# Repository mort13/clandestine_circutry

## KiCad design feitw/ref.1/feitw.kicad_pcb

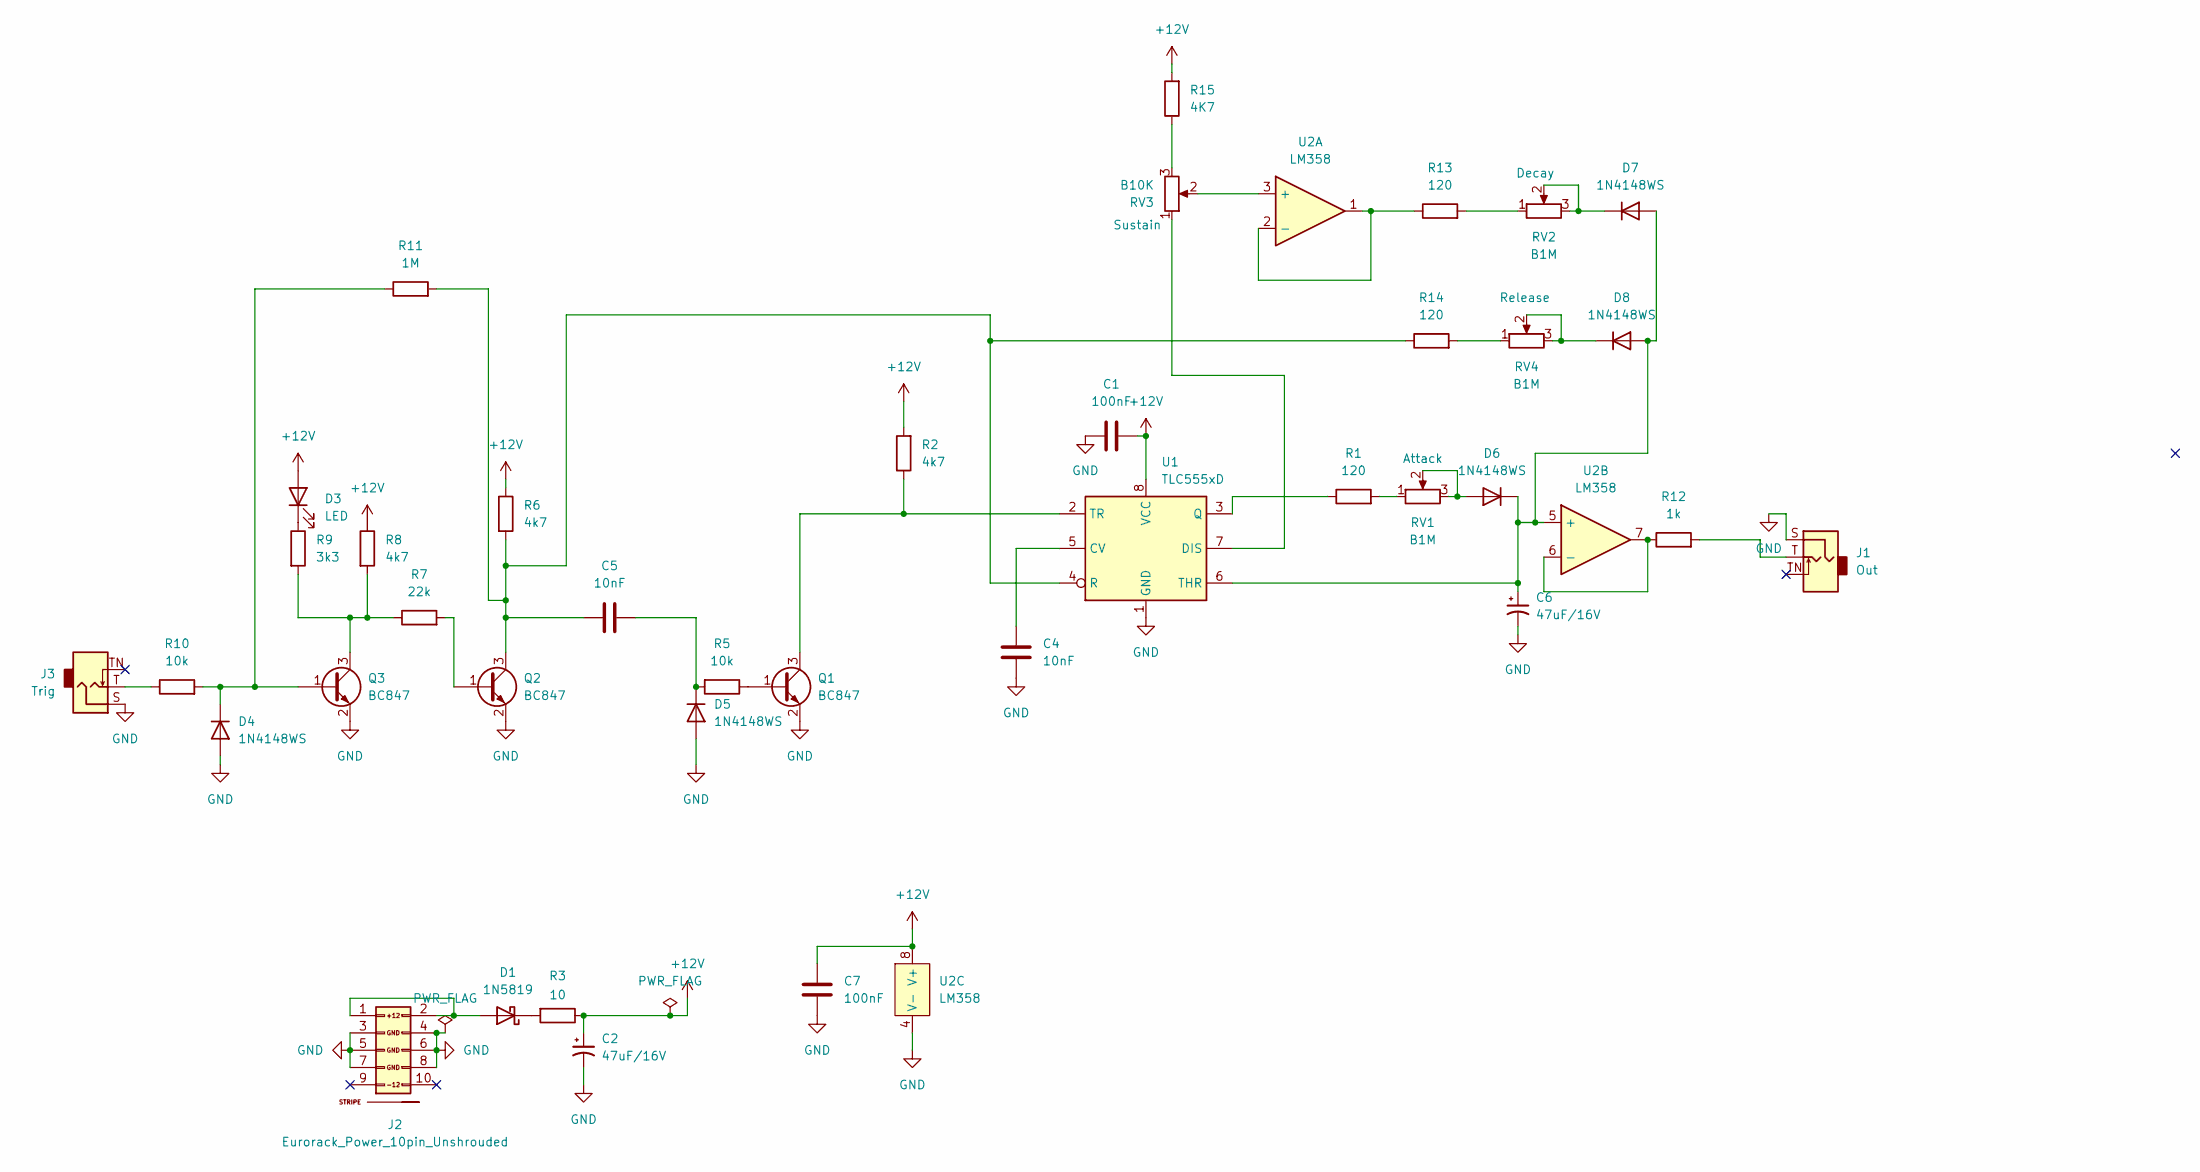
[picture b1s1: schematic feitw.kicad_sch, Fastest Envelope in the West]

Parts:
C1, C7: 100nF; C_Disc_D3.0mm_W1.6mm_P2.50mm
C2: 10uF_5x5.3_16V; CP_Radial_D4.0mm_P2.00mm; Part Number VE-470M1CTR-0505; JLCPCB ID C134798
C4, C5: 10nF; C_Disc_D3.0mm_W1.6mm_P2.50mm
C6: 47uF_5x5.3_16V; CP_Radial_D4.0mm_P2.00mm; Part Number VE-470M1CTR-0505; JLCPCB ID C134798
D1: 1N5819; D_DO-41_SOD81_P2.54mm_Vertical_AnodeUp
D3: LED; LED_D1.8mm_W3.3mm_H2.4mm
D4, D5, D6, D7, D8: 1N4148WS; D_SOD-323
J1: Out; PJ398SM
J2: Eurorack_Power_10pin_Unshrouded; PinSocket_2x05_P2.54mm_Vertical; Part Number 1-1002FBV0T
J3: Trig; PJ398SM
Q1, Q2, Q3: BC847; SOT-23
R1, R13, R14: 120; R_Axial_DIN0204_L3.6mm_D1.6mm_P1.90mm_Vertical
R2, R6, R8: 4k7; R_Axial_DIN0204_L3.6mm_D1.6mm_P1.90mm_Vertical
R3: 10; R_Axial_DIN0204_L3.6mm_D1.6mm_P1.90mm_Vertical
R5, R10: 10k; R_Axial_DIN0204_L3.6mm_D1.6mm_P1.90mm_Vertical
R7: 22k; R_Axial_DIN0204_L3.6mm_D1.6mm_P1.90mm_Vertical
R9: 3k3; R_Axial_DIN0204_L3.6mm_D1.6mm_P1.90mm_Vertical
R11: 1M; R_Axial_DIN0204_L3.6mm_D1.6mm_P1.90mm_Vertical
R12: 1k; R_Axial_DIN0204_L3.6mm_D1.6mm_P1.90mm_Vertical
R15: 4K7; R_Axial_DIN0204_L3.6mm_D1.6mm_P1.90mm_Vertical
RV1, RV2, RV4: B1M; Potentiometer_Alpha_RD901F-40-00D_Single_Vertical_withhole
RV3: B10K; Potentiometer_Alpha_RD901F-40-00D_Single_Vertical_withhole
U1: TLC555xD; SOIC-8_3.9x4.9mm_P1.27mm
U2: LM358; SOIC-8_3.9x4.9mm_Pitch1.27mm; JLCPCB ID C7951

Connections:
+12V: C1.1, C2.1, C7.2, D3.2 (A), R2.2, R3.1, R6.1, R8.1, R15.2, U1.8 (VCC), U2.8 (V+)
GND: C1.2, C2.2, C4.2, C6.2, C7.1, D4.2 (A), D5.2 (A), J1.S, J2.3 (GND), J2.4 (GND), J2.5 (GND), J2.6 (GND), J2.7 (GND), J2.8 (GND), J3.S, Q1.2 (E), Q2.2 (E), Q3.2 (E), U1.1 (GND), U2.4 (V-)
unnamed: D1.2 (A), J2.1 (+12V), J2.2 (+12V)
unnamed: D1.1 (K), R3.2
unnamed: D3.1 (K), R9.1
unnamed: D4.1 (K), Q3.1 (B), R10.2, R11.1
unnamed: C5.2, D5.1 (K), R5.2
unnamed: D6.2 (A), RV1.2, RV1.3
unnamed: C6.1, D6.1 (K), D7.2 (A), D8.2 (A), U1.6 (THR), U2.5 (+)
unnamed: D7.1 (K), RV2.2, RV2.3
unnamed: D8.1 (K), RV4.2, RV4.3
unnamed: J1.T, R12.2
unnamed: J3.T, R10.1
unnamed: Q1.1 (B), R5.1
unnamed: Q1.3 (C), R2.1, U1.2 (TR)
unnamed: Q2.1 (B), R7.2
unnamed: C5.1, Q2.3 (C), R6.2, R11.2, R14.1, U1.4 (R)
unnamed: Q3.3 (C), R7.1, R8.2, R9.2
unnamed: R1.2, RV1.1
unnamed: R13.2, RV2.1
unnamed: R14.2, RV4.1
unnamed: R15.1, RV3.3
unnamed: C4.1, U1.5 (CV)
unnamed: RV3.1, U1.7 (DIS)
unnamed: R1.1, U1.3 (Q)
unnamed: RV3.2, U2.3 (+)
unnamed: R13.1, U2.1, U2.2 (-)
unnamed: R12.1, U2.6 (-), U2.7

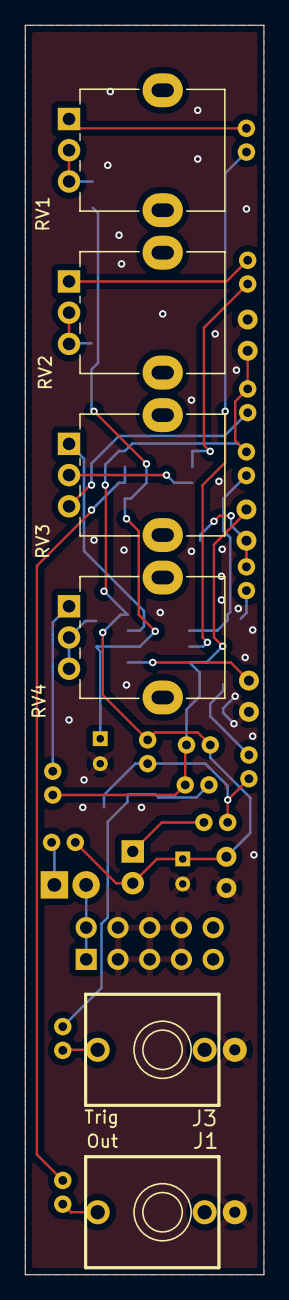
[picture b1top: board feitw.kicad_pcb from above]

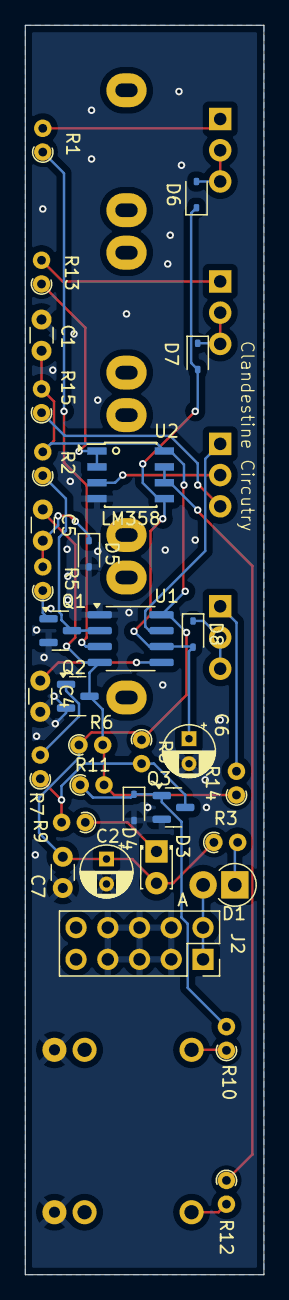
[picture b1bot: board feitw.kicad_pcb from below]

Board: 2 copper layers, 19.1 x 100.0 mm, 39 parts (33 on the bottom side), 28 nets.

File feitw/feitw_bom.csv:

"Reference","Value","Datasheet","Footprint","Qty","DNP"
"C1,C7","100nF","~","Capacitor_SMD:C_0805_2012Metric_Pad1.18x1.45mm_HandSolder","2",""
"C2","10uF_5x5.3_16V","","Capacitor_THT:CP_Radial_D4.0mm_P2.00mm","1",""
"C4,C5","10nF","~","Capacitor_SMD:C_0805_2012Metric_Pad1.18x1.45mm_HandSolder","2",""
"C6","47uF_5x5.3_16V","","Capacitor_THT:CP_Radial_D4.0mm_P2.00mm","1",""
"D1","1N5819","http://www.vishay.com/docs/88525/1n5817.pdf","Diode_THT:D_DO-41_SOD81_P2.54mm_Vertical_AnodeUp","1",""
"D2","LED","~","LED_THT:LED_D1.8mm_W3.3mm_H2.4mm","1",""
"D4,D5,D6,D7,D8","1N4148WS","https://www.vishay.com/docs/85751/1n4148ws.pdf","Diode_SMD:D_SOD-323","5",""
"J1","Out","~","mort_mix:PJ398SM","1",""
"J2","Eurorack_Power_10pin_Unshrouded","","mort_mix:PinHeader_2x05_P2.54mm_Vertical_shrouded","1",""
"J3","Trig","~","mort_mix:PJ398SM","1",""
"Q1,Q2,Q3,Q4","BC847","http://www.infineon.com/dgdl/Infineon-BC847SERIES_BC848SERIE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","Package_TO_SOT_SMD:SOT-23","4",""
"R1,R13,R14","120","~","Resistor_SMD:R_0805_2012Metric_Pad1.20x1.40mm_HandSolder","3",""
"R2,R6,R8","4k7","~","Resistor_SMD:R_0805_2012Metric_Pad1.20x1.40mm_HandSolder","3",""
"R3","10","~","Resistor_THT:R_Axial_DIN0204_L3.6mm_D1.6mm_P1.90mm_Vertical","1",""
"R4","3k3","~","Resistor_SMD:R_0805_2012Metric_Pad1.20x1.40mm_HandSolder","1",""
"R5,R10","10k","~","Resistor_SMD:R_0805_2012Metric_Pad1.20x1.40mm_HandSolder","2",""
"R7","22k","~","Resistor_SMD:R_0805_2012Metric_Pad1.20x1.40mm_HandSolder","1",""
"R11","1M","~","Resistor_SMD:R_0805_2012Metric_Pad1.20x1.40mm_HandSolder","1",""
"R12","1k","~","Resistor_SMD:R_0805_2012Metric_Pad1.20x1.40mm_HandSolder","1",""
"R15","4K7","~","Resistor_SMD:R_0805_2012Metric_Pad1.20x1.40mm_HandSolder","1",""
"RV1,RV2,RV4","A1M","~","mort_mix:Potentiometer_Alpha_RD901F-40-00D_Single_Vertical_withhole","3",""
"RV3","A10K","~","mort_mix:Potentiometer_Alpha_RD901F-40-00D_Single_Vertical_withhole","1",""
"U1","TLC555xD","http://www.ti.com/lit/ds/symlink/tlc555.pdf","Package_SO:SOIC-8_3.9x4.9mm_P1.27mm","1",""
"U2","LM358","","PCM_4ms_Package_SOIC:SOIC-8_3.9x4.9mm_Pitch1.27mm","1",""

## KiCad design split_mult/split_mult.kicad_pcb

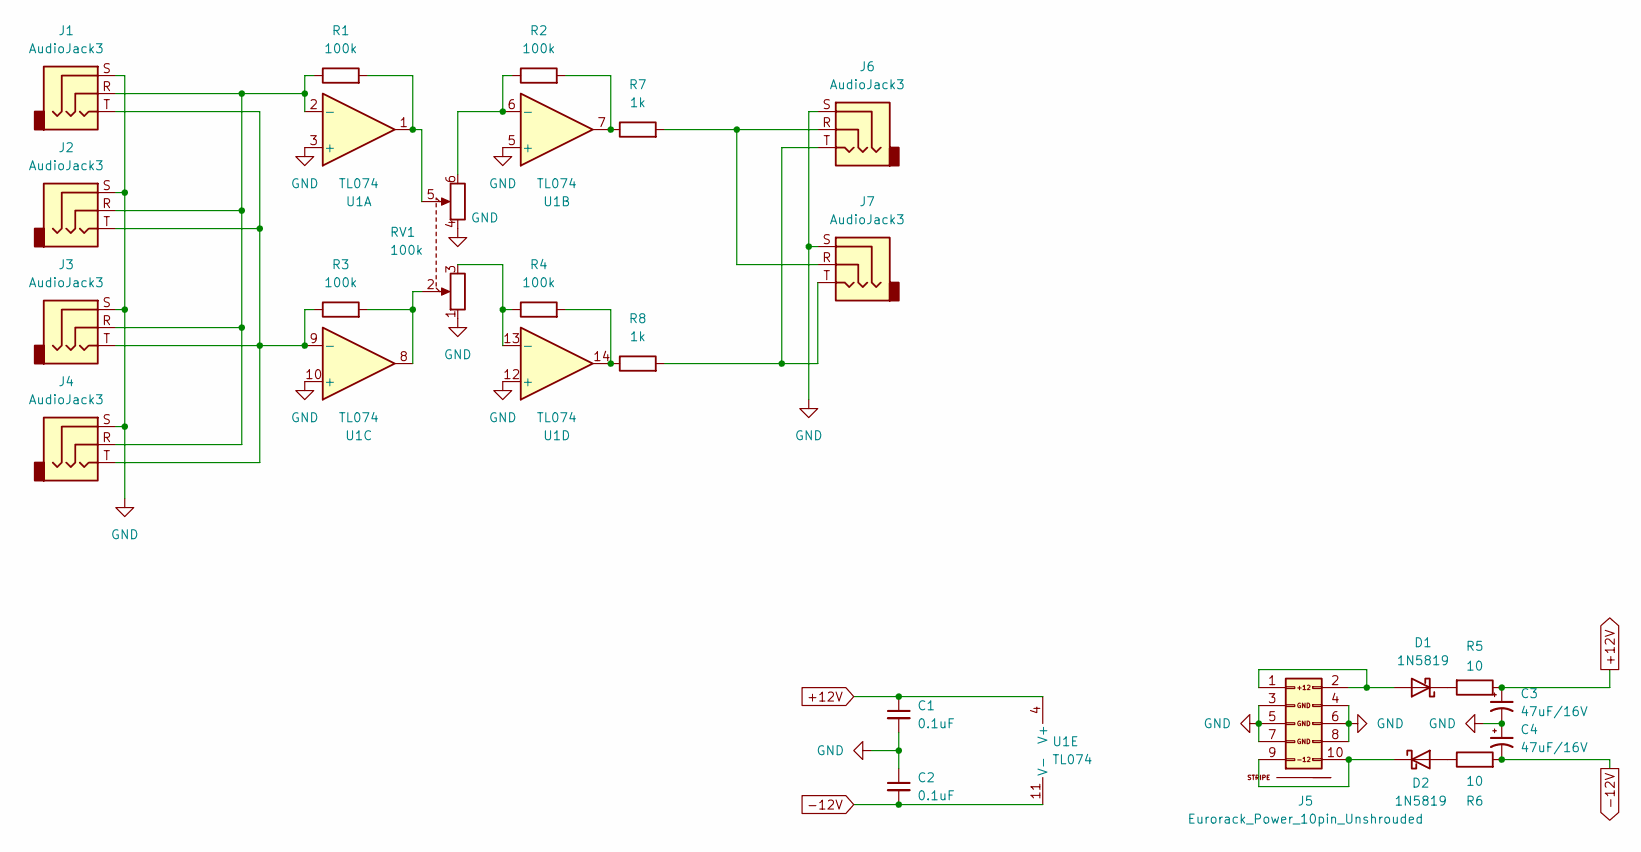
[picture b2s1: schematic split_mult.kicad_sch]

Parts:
C1, C2: 0.1uF_0603_16V; C_Disc_D5.0mm_W2.5mm_P5.00mm; Part Number 0603YC104KAT2A; JLCPCB ID C14663
C3, C4: 47uF_5x5.3_16V; CP_Radial_D4.0mm_P2.00mm; Part Number VE-470M1CTR-0505; JLCPCB ID C134798
D1, D2: 1N5819; D_DO-41_SOD81_P2.54mm_Vertical_KathodeUp
J1, J2, J3, J4, J6, J7: AudioJack3; Jack_3.5mm_QingPu_WQP-PJ366ST_Vertical
J5: Eurorack_Power_10pin_Unshrouded; PinSocket_2x05_P2.54mm_Vertical; Part Number 1-1002FBV0T
R1, R2, R3, R4: 100k; R_Axial_DIN0207_L6.3mm_D2.5mm_P2.54mm_Vertical
R5, R6: 10; R_Axial_DIN0207_L6.3mm_D2.5mm_P2.54mm_Vertical
R7, R8: 1k; R_Axial_DIN0207_L6.3mm_D2.5mm_P2.54mm_Vertical
RV1: 100k; Potentiometer_Bourns_PTV112-4_Dual_Vertical
U1: TL074; DIP-14_W7.62mm

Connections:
+12V: C1.1, C3.1, R5.1, U1.4 (V+)
-12V: C2.2, C4.2, R6.2, U1.11 (V-)
GND: C1.2, C2.1, C3.2, C4.1, J1.S, J2.S, J3.S, J4.S, J5.3 (GND), J5.4 (GND), J5.5 (GND), J5.6 (GND), J5.7 (GND), J5.8 (GND), J6.S, J7.S, RV1.1, RV1.4, U1.3 (+), U1.5 (+), U1.10 (+), U1.12 (+)
unnamed: D1.2 (A), J5.1 (+12V), J5.2 (+12V)
unnamed: D1.1 (K), R5.2
unnamed: D2.2 (A), R6.1
unnamed: D2.1 (K), J5.9 (-12V), J5.10 (-12V)
unnamed: J6.R, J7.R, R7.2
unnamed: J6.T, J7.T, R8.2
unnamed: R1.2, RV1.5, U1.1
unnamed: R2.2, R7.1, U1.7
unnamed: R3.2, RV1.2, U1.8
unnamed: R4.2, R8.1, U1.14
unnamed: J1.R, J2.R, J3.R, J4.R, R1.1, U1.2 (-)
unnamed: R2.1, RV1.6, U1.6 (-)
unnamed: J1.T, J2.T, J3.T, J4.T, R3.1, U1.9 (-)
unnamed: R4.1, RV1.3, U1.13 (-)

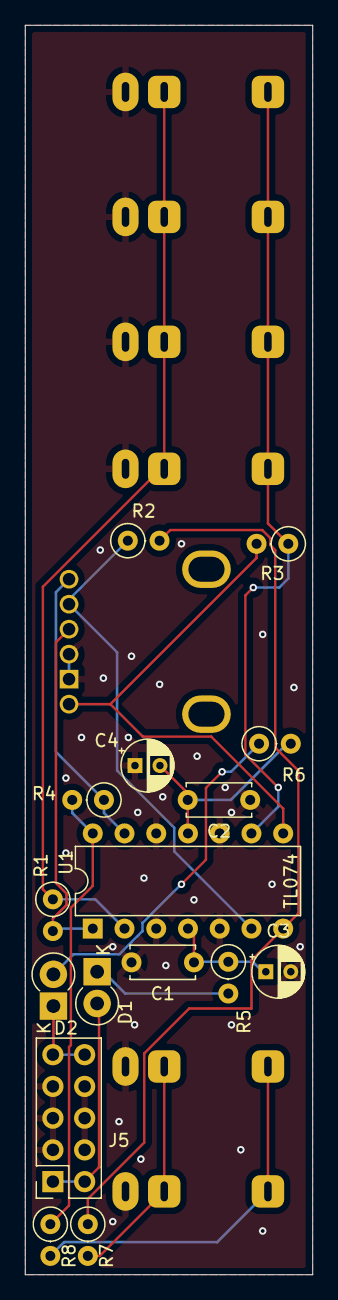
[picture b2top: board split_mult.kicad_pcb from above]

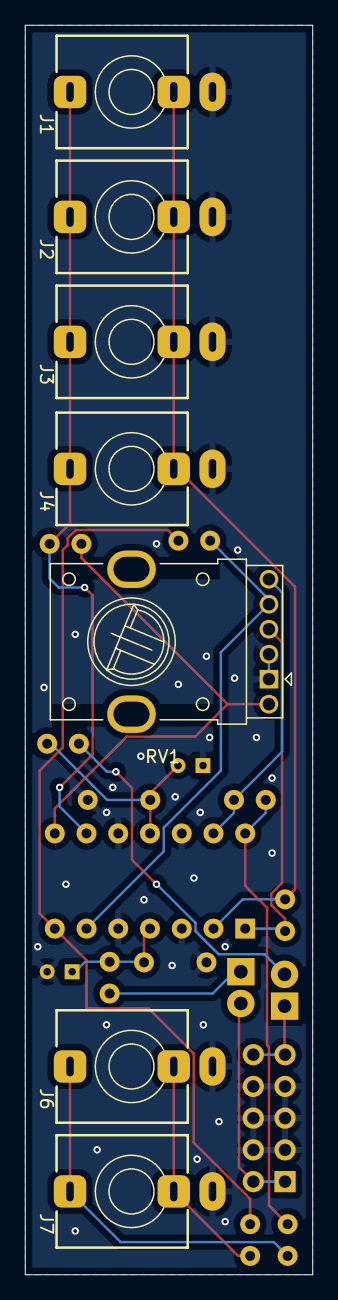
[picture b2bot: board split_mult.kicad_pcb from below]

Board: 2 copper layers, 23.0 x 100.0 mm, 23 parts (7 on the bottom side), 17 nets.
